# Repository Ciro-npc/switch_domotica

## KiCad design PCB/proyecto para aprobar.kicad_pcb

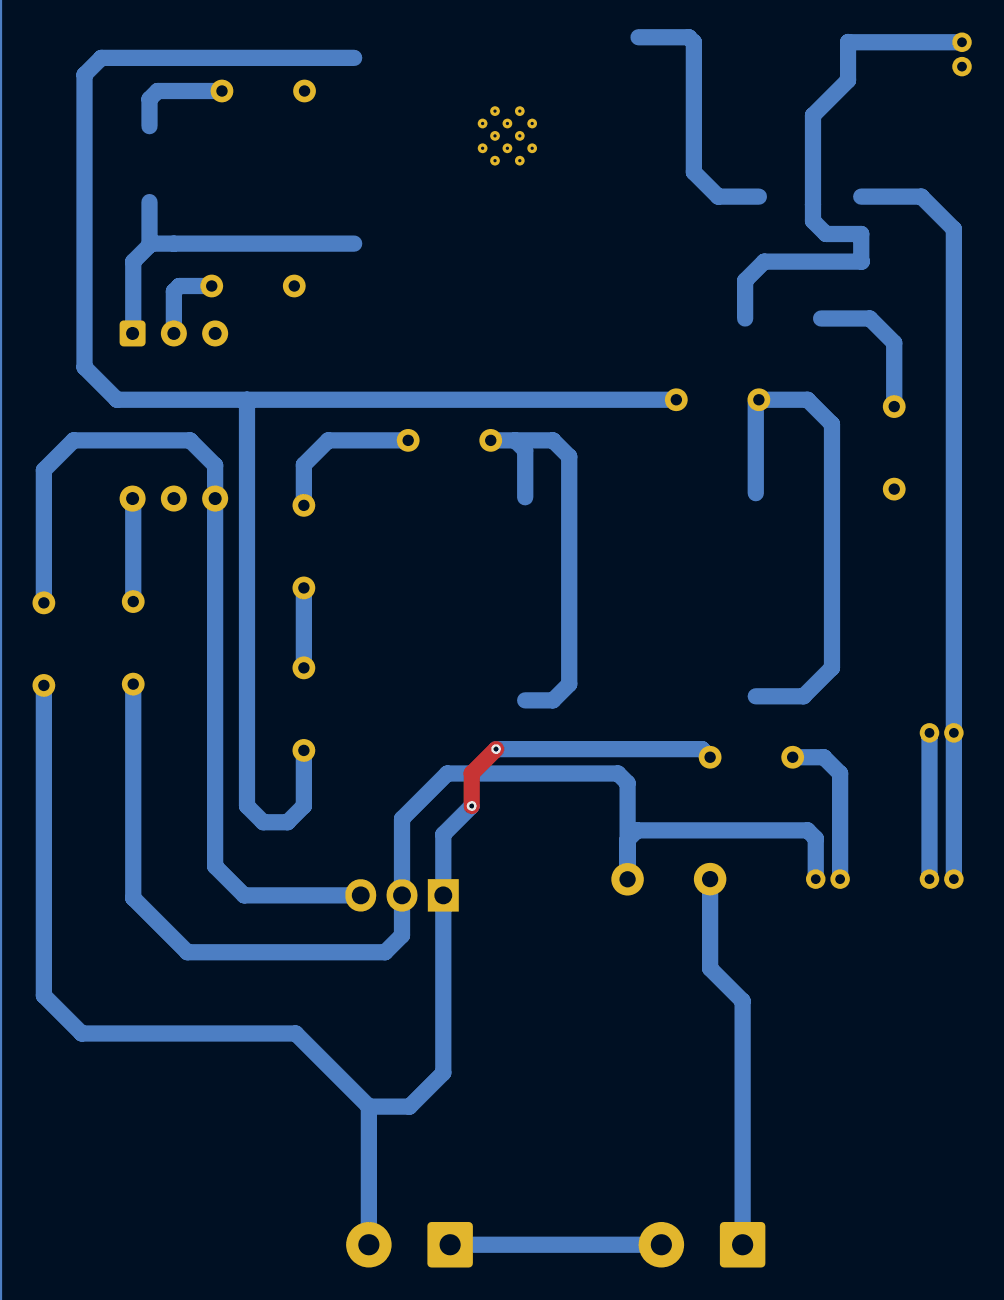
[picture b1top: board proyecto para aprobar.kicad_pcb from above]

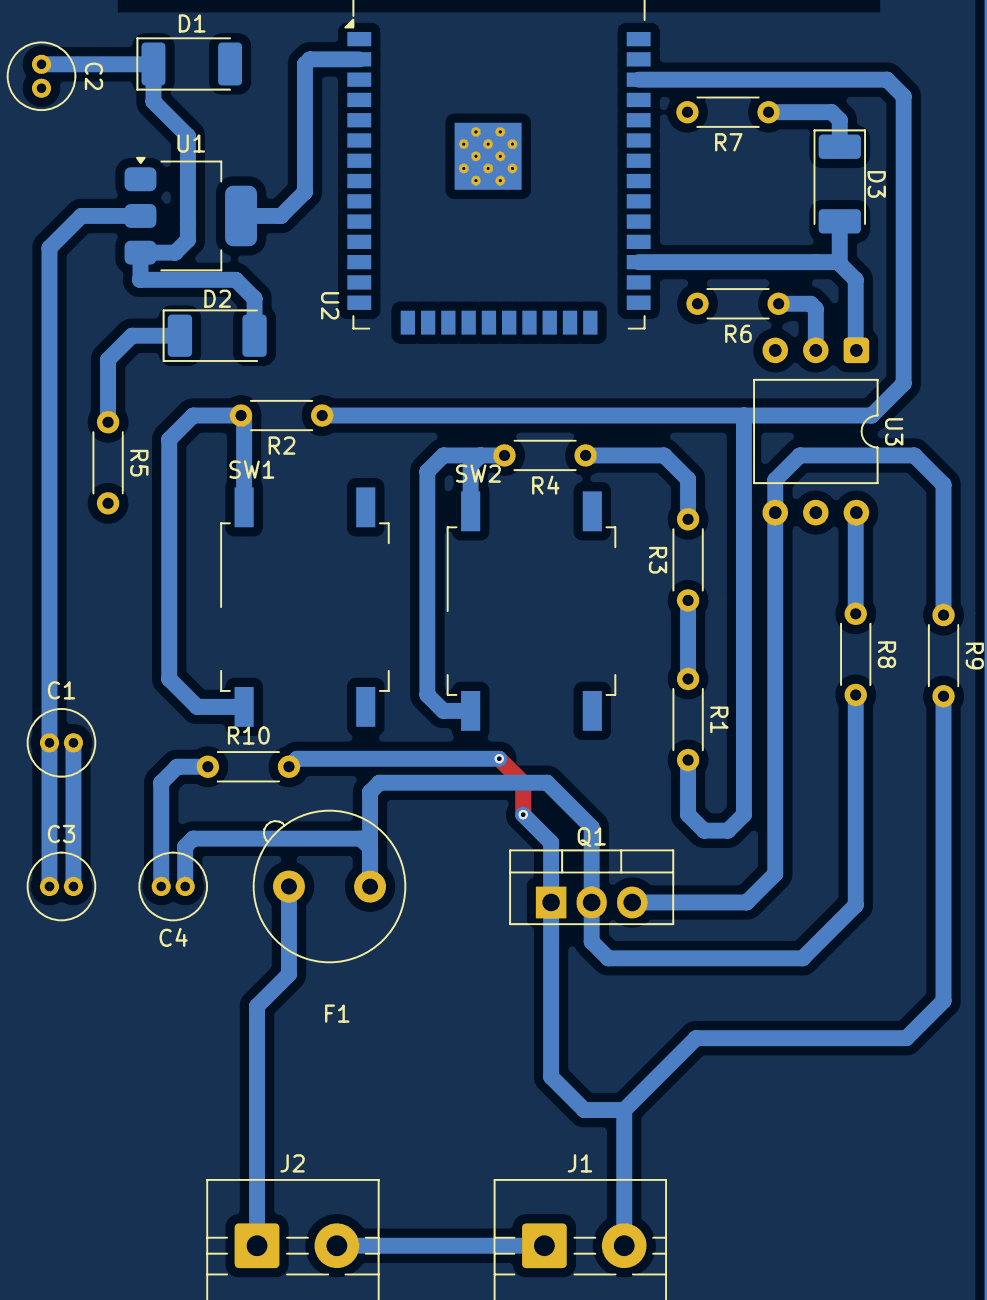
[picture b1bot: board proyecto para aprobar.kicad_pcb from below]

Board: 2 copper layers, 26 parts (26 on the bottom side), 19 nets.

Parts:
C1: 100uF; C_Radial_D4.0mm_H5.0mm_P1.50mm
C2, C3: 10uF; C_Radial_D4.0mm_H5.0mm_P1.50mm
C4: C; C_Radial_D4.0mm_H5.0mm_P1.50mm
D1: 1N5711UR; D_MELF
D2, D3: LED; LED_2010_5025Metric_Pad1.52x2.65mm_HandSolder
F1: 2-10 AMP; Fuseholder_TR5_Littelfuse_No560_No460
J1: LOAD; TerminalBlock_MaiXu_MX126-5.0-02P_1x02_P5.00mm
J2: PWR; TerminalBlock_MaiXu_MX126-5.0-02P_1x02_P5.00mm
Q1: BT138-600; TO-220-3_Vertical
R1, R3: 12k; R_Axial_DIN0204_L3.6mm_D1.6mm_P5.08mm_Horizontal
R2, R4: 470; R_Axial_DIN0204_L3.6mm_D1.6mm_P5.08mm_Horizontal
R5: 1k; R_Axial_DIN0204_L3.6mm_D1.6mm_P5.08mm_Horizontal
R6, R7: 560R; R_Axial_DIN0204_L3.6mm_D1.6mm_P5.08mm_Horizontal
R8: 56R; R_Axial_DIN0204_L3.6mm_D1.6mm_P5.08mm_Horizontal
R9: 330R; R_Axial_DIN0204_L3.6mm_D1.6mm_P5.08mm_Horizontal
R10: 39R; R_Axial_DIN0204_L3.6mm_D1.6mm_P5.08mm_Horizontal
SW1, SW2: SW_MEC_5G; SW_MEC_5GSH9
U1: AMS1117-3.3; SOT-223-3_TabPin2
U2: ESP32-WROOM-32
U3: MOC3041M; DIP-6_W10.16mm

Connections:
/#EN: R3.2, R4.1
/IO0: R1.2, R2.1, U2.36 (IO22)
/Signal: D3.2 (A), U2.27 (IO16), U3.1
GND: C1.2, C2.2, C3.2, R5.2, R6.2, R7.2, SW1.3 (B), SW1.4 (B), SW2.3 (B), SW2.4 (B), U1.1 (GND), U2.1 (GND), U2.15 (GND), U2.38 (GND), U2.39 (GND)
unnamed: C4.2, R10.1
unnamed: D2.1 (K), R5.1
unnamed: D3.1 (K), R7.1
unnamed: J1.1, J2.2
unnamed: J1.2, Q1.1 (A1), R9.2, R10.2
unnamed: F1.2, J2.1
unnamed: C4.1, F1.1, Q1.2 (A2), R8.2
unnamed: Q1.3 (G), R9.1, U3.4
unnamed: R2.2, SW1.1 (A), SW1.2 (A)
unnamed: R4.2, SW2.1 (A), SW2.2 (A)
unnamed: R6.1, U3.2
unnamed: R8.1, U3.6
VDD: R1.1, R3.1
VDD3v3: C1.1, C3.1, U1.2 (VO), U2.2 (VDD)
VDD5V: C2.1, D1.1 (K), D2.2 (A), U1.3 (VI)

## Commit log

2026-06-12 Create 1
2026-06-12 se añadio la pcb temporal del proyecto
    esta pcb esta sujeta a cambios es solo un prototipo
